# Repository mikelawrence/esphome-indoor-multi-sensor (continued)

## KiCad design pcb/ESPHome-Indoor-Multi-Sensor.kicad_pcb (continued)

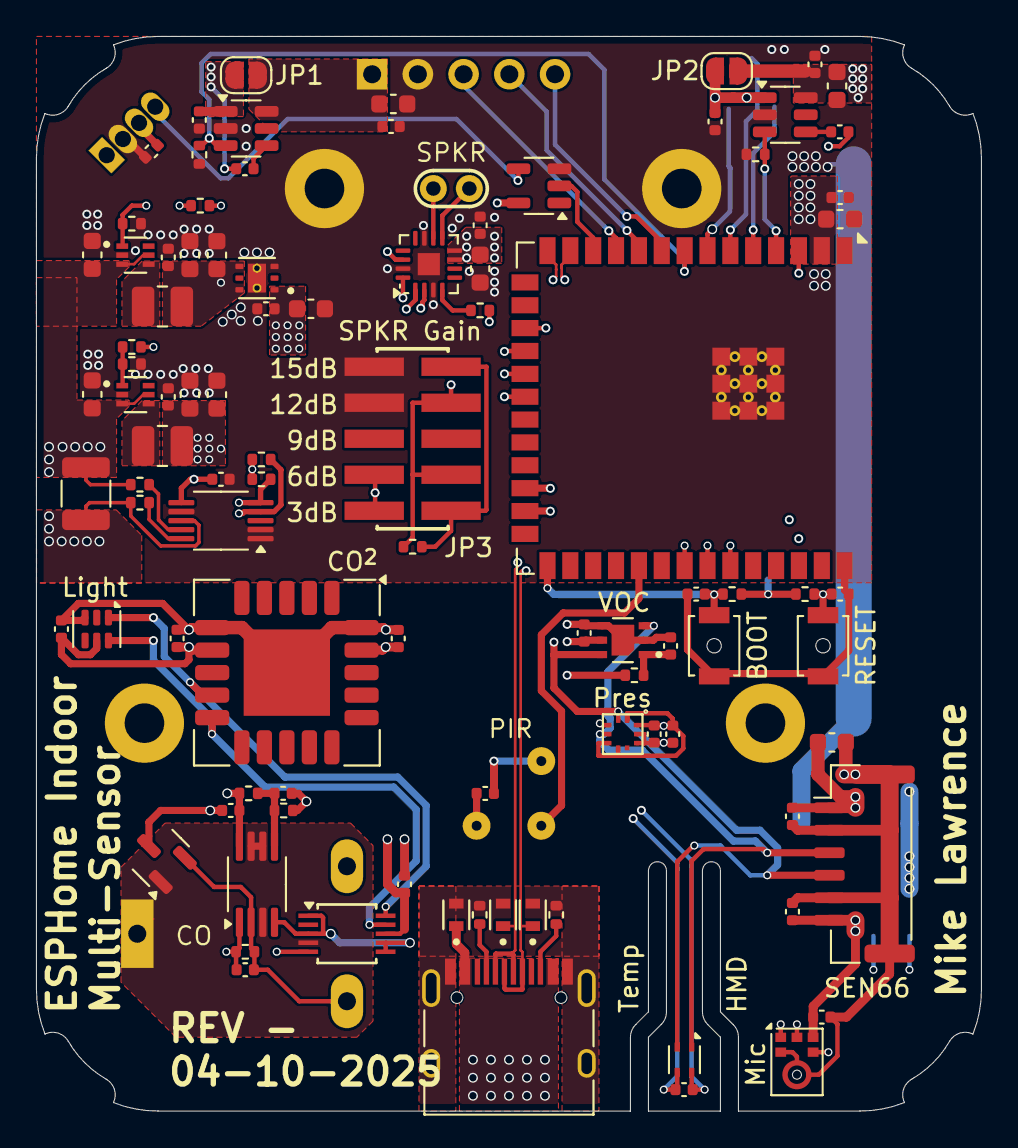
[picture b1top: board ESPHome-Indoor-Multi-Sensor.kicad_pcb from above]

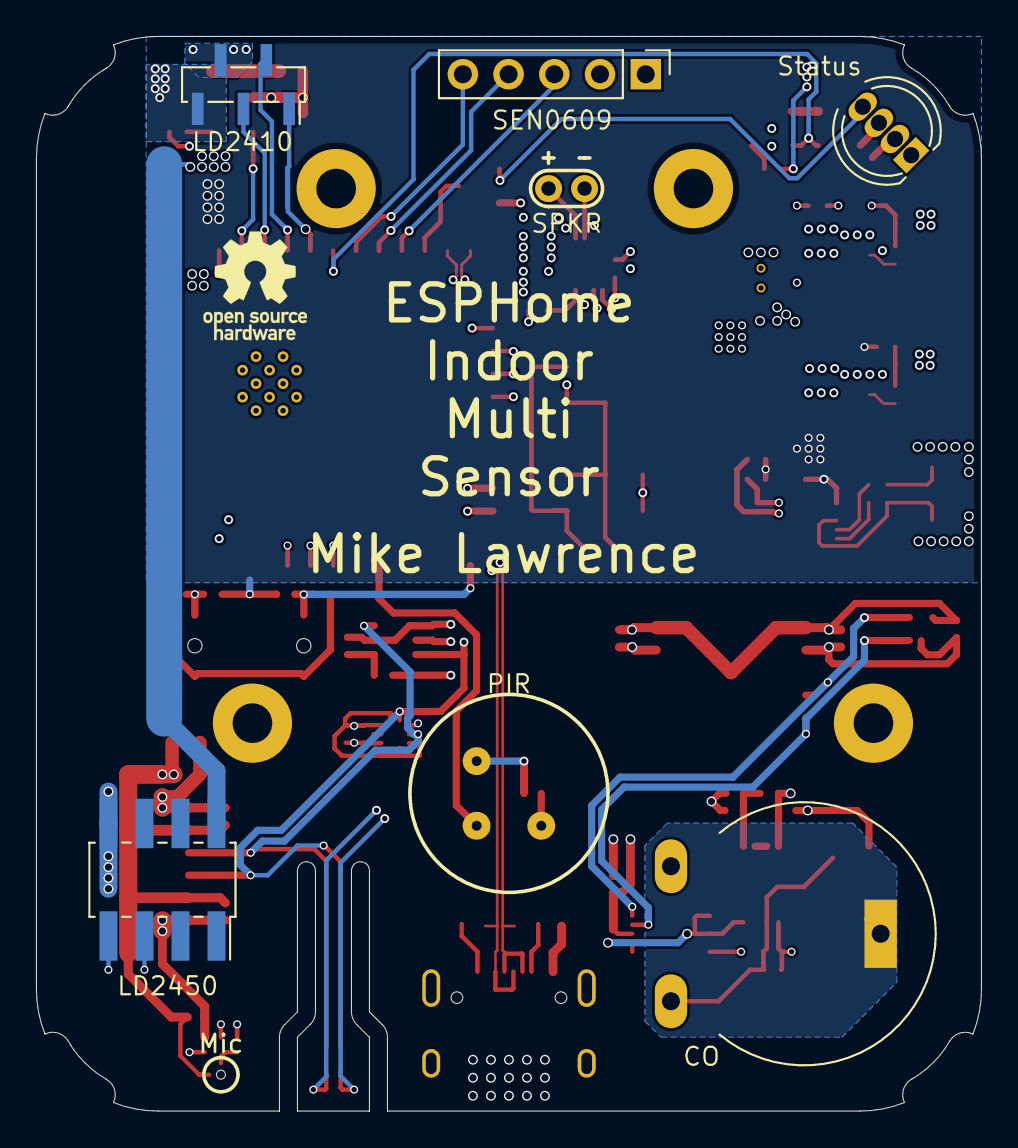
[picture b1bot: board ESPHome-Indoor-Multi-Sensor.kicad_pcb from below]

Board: 4 copper layers, 52.5 x 59.7 mm, 106 parts (8 on the bottom side), 52 nets.

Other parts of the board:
TEXT1: OSHW-Logo_5.7x6mm_SilkScreen

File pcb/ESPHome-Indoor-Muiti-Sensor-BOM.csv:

"Qty","Reference","Value","Description","DNP","Manufacturer","Part Number"
"13","C1,C4,C5,C6,C8,C26,C29,C30,C31,C35,C38,C40,C41","1uF","Capacitor, 1uF, MLCC, 25V, X5R, 10%, 0402","","Samsung","CL05A105KA5NQNC"
"16","C10,C11,C14,C18,C21,C24,C25,C27,C28,C32,C33,C36,C37,C39,C42,C43","100nF","Capacitor, 100nF, MLCC, 50V, X7R, 10%, 0402","","Samsung","CL05B104KB54PNC"
"12","C2,C3,C12,C13,C15,C16,C17,C19,C20,C22,C23,C34","22uF","Capacitor, 22uF, MLCC, 6.3V, X5R, 20%, 0603","","Murata","GRM188R60J226MEA0D"
"2","C7,C9","1nF","Capacitor, 1nF, MLCC, 50V, X7R, 10%, 0402","","KYOCERA AVX","04023C102KAT2A"
"1","D1","ESDA25P35-1U1M","TVS, Unidirectional high power, QFN-2","","STMicroelectronics","ESDA25P35-1U1M"
"1","D4","NeoPixel_THT","RGB LED with integrated controller, 5mm/8mm LED package","","Adafruit","1938"
"2","D2,D3","ESDA7P60-1U1M","TVS, Unidirectional high power, QFN-2","","STMicroelectronics","ESDA7P60-1U1M"
"1","J1","SEN66","6-Position, 1.25 mm pitch, Wire-to-Board connector","","JST","BM06B-GHS-TBT"
"1","J2","USB-C","Connector, USB 2.0, 16P, Type-C, Receptacle","","Phoenix Contact","1332645"
"1","J3","SEN0609","Generic connector, 2.54mm spacing, single row, 01x05 (TLW-105-06-T-S)","","Samtec","CES-105-01-T-S"
"1","J4","LD2410","Generic connector, 1.27mm spacing, single row, 01x05","","Samtec","RSM-105-02-S-S"
"1","J5","SPKR","Solder Holes for up to 24 ga wire","","Same Sky","CMS-251437-24SP-X8 "
"1","J6","LD2450","Socket, 8 position, 2mm spacing, dual row, 02x04, SMT","","Molex","79109-1003"
"1","JP3","Gain","Header, 10 position, 2mm spacing, dual row, 02x05, SMT","","Samtec","TMM-105-01-L-D-SM-P-TR"
"2","L1,L2","1uH","Inductor, 1uH, 3.3A, 20%, 1008","","Murata","DFE252012F-1R0M=P2"
"1","MK1","ICS-43434","TDK InvenSense MEMS Microphone, 24-bit I2S, 65 dBA SNR, LGA-6","","TDK InvenSense","ICS-43434"
"1","Q1","MMBFJ201","20mA min, 35V, 30mOhm max, 3-10V Vgs(off), N-Channel JFET, SOT-23","","Onsemi","MMBFJ201"
"1","R3","499KΩ","Resistor, 499KΩ, 62.5mW, 1%, 0402","","Vishay / Dale","CRCW0402499KFKED"
"1","R5","634KΩ","Resistor, 634KΩ, 62.5mW, 1%, 0402","","Vishay / Dale","CRCW0402634KFKED"
"1","R6","453KΩ","Resistor, 453KΩ, 62.5mW, 1%, 0402","","Vishay / Dale","CRCW0402453KFKED"
"1","R11","150mΩ","Current Sense Resistor, 150mΩ, 500mW, 1%, 1210","","Panasonic","ERJ-14BSFR15U"
"1","R16","4.7Ω","Resistor, 4.7Ω, 62.5mW, 1%, 0402","","Vishay / Dale","CRCW04024R70FKED"
"1","R17","64.9KΩ","Resistor, 64.9KΩ, 62.5mW, 1%, 0402","","Vishay / Dale","CRCW040264K9FKED "
"1","R21","133KΩ","Resistor, 133KΩ, 62.5mW, 1%, 0402","","Vishay / Dale","CRCW0402133KFKED"
"6","R1,R2,R4,R7,R13,R18","100KΩ","Resistor, 100KΩ, 62.5mW, 1%, 0402","","Vishay / Dale","CRCW0402100KFKED"
"2","R10,R12","10Ω","Resistor, 10Ω, 62.5mW, 1%, 0402","","Vishay / Dale","CRCW040210R0FKEE"
"2","R14,R15","10KΩ","Resistor, 10KΩ, 62.5mW, 1%, 0402","","Vishay / Dale","CRCW040210K0FKED"
"2","R19,R20","5.1KΩ","Resistor, 5.1KΩ, 62.5mW, 1%, 0402","","Vishay / Dale","CRCW04025K10FKED"
"2","R8,R9","DNP","Resistor, Do Not Populate, 0402","DNP","",""
"1","SW1","BOOT","Switch, SMD","","Omron","B3U-1000P"
"1","SW2","RESET","Switch, SMD","","Omron","B3U-1000P"
"1","U3","SN74LV1T34DBV","IC, Single Power Supply, Single Buffer GATE, CMOS Logic, Level Shifter, SOT-23-5","","Texas Instruments","SN74LV1T34DBV"
"1","U5","MAX98357A","Mono DAC with amplifier, I2S, PCM, TDM, 32-bit, 96khz, 3.2W, TQFP-16","","Maxim","MAX98357AETE"
"1","U6","TLV75533PDRV","500mA Low Dropout Voltage Regulator, Fixed Output 3.3V, WSON6","","Texas Instruments","TLV75533PDRV"
"1","U8","ESP32-S3-WROOM-2-N32R16V","RF Module, ESP32-S3 SoC, Wi-Fi 802.11b/g/n, Bluetooth, BLE, 32-bit, 3.3V, onboard antenna, SMD","","Espressif","ESP32-S3-WROOM-2-N32R16V"
"1","U9","INA228","IC, High-Side or Low-Side Measurement, Bi-Directional Current and Power Monitor (0-85V) with I2C, SMBus-, and PMBus-Compatible Interface, VSSOP-10","","Texas Instruments","INA228AIDGSR"
"1","U10","TSL2591","Light to digital converter, 2.7 to 3.6V Vdd, DFN-6","","AMS","TSL2591"
"1","U11","SGP41","Indoor Air Quality Sensor, MOx based, DFN-6","","Sensirion","SGP41-D-R4 "
"1","U12","SCD41","Photoacoustic CO2 sensor, I2C, 2.4-5.5 V, High accuracy  400 - 5000 ppm","","Sensirion","SCD41-D-R2"
"1","U13","BMP581","Barometric Pressure Sensor, 24-bit, Low-power and Low-noise, SMD","","Bosch Sensortec ","BMP581"
"1","U14","MCP6042","Dual Operational Amplifiers, Rail-to-Rail Input/Output, MSOP-8","","Microchip","MCP6042T-I/MS"
"1","U15","ADS1115IDGS","Ultra-Small, Low-Power, I2C-Compatible, 860-SPS, 16-Bit ADCs With Internal Reference, Oscillator, and Programmable Comparator, VSSOP-10","","Texas Instruments","ADS1115IDGS"
"1","U16","SHT45","Digital Humidity and Temperature Sensor, ±1%RH, ±0.1°C, I2C, 1.08-3.6V, 16bit, DFN-4","","Sensirion","SHT45-AD1B-R2"
"1","U17","EKMC1603111","Passive Infrared (PIR) Motion Sensor, THT","","Panasonic","EKMC1603111"
"1","U18","TGS5141","Carbon Monoxide Sensor, Long life, THT","","Figaro","TGS5141-P00"
"2","U1,U2","TPS22917DBV","1V to 5.5V, 2A, 80mΩ Ultra-Low Leakage Load Switch, SOT23-6","","Texas Instruments","TPS22917DBV"
"2","U4,U7","TLV62568DRL","High Efficiency Synchronous Buck Converter, Adjustable Output 0.6V-5.5V, 1A, SOT-563-6","","Texas Instruments","TLV62568DRL"

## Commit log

2025-04-11 Initial commit.
2025-04-12 Round out the enclosure section.
2025-04-12 Cleanup the PCB section.
2025-04-12 Add more info to the main README.
2025-04-12 SLight change to schematic.
2025-06-11 Minor changes
    Separate SEN66 on a separate I2C bus.
    Add WIFi Antenna cutout.
    Beef-up Power and Ground connections to SEN66.
2025-06-24 Add ESPHome Installation and Configuration
    Add customizable configurations
    Add Workflows to automatically build ESPHome binaries.
    Add documentation.
2025-06-24 All substitutions must be strings
2025-06-24 Remove Update Rate configuration settings
2025-06-24 Support vent_use_humidity and vent_use_co2 substitutions
2025-06-24 Add configuration details to the Github page
2025-06-24 CI Workflow changes
    CI spawns on push to dev
    CI only builds latest stable ESPHome
2025-06-24 CI only builds ESPHome stable
2025-06-24 Fix CI path error
2025-06-25 Update ci.yml
    Fix CI path error
2025-06-25 rename config files
2025-06-25 Update config file names inside config files
2025-06-25 Update ci.yml
    Allow for 4 parallel runs
2025-06-25 Correct file names in workflows
2025-06-30 Force line endings to LF
2025-06-30 Workflow updates
    Add automatic Release when merging a pull request into main.
    Next the ESP32 build process is kicked off for all config files.
    Next the build files are published to the Release as assets.
    And finally Github Pages are published supporting the new Release.
2025-06-30 Substantial config changes
    Config filenames now include esp32-s3.
    Simplification of substitutions
2025-06-30 Update Github Pages
    Finish out the config substitutions.
2025-06-30 Minor update to Github Pages
2025-06-30 Fix miss-match with Create Release workflow and downstream workflows
2025-06-30 Update Github Pages
2025-06-30 Another update to Github Pages
2025-06-30 Update publish-firmware.yml
    Eliminate checks on publish-firmware
2025-06-30 Support External Component 2591
    Fix compile ESP32 compile error
2025-06-30 Changes to TSL2591 configuration
    Looking for better low light and stopping the both sensors are 0 warning
2025-06-30 Slight Changes to Github Pages
2025-06-30 Bump cardinalby/git-get-release-action from 1.2.4 to 1.2.5
    Bumps [cardinalby/git-get-release-action](https://github.com/cardinalby/git-get-release-action) from 1.2.4 to 1.2.5.
    - [Release notes](https://github.com/cardinalby/git-get-release-action/releases)
    - [Commits](https://github.com/cardinalby/git-get-release-action/compare/1.2.4...1.2.5)
    ---
    updated-dependencies:
    - dependency-name: cardinalby/git-get-release-action
2025-06-30 CO2 changes
    Fix missing update on CO2 Calibration Date Sensor
    Configuration variable changed to automatic_self_calibration which is already in consts.py
2025-07-01 Releases are no longer automatic when PR is merger into main
2025-07-01 Include more yaml files for CI workflow
2025-07-01 Try to fix checkout in CI. PR's check out main
2025-07-01 Undo checkout changes in CI workflow
2025-07-01 Default substitution changes
2025-07-01 Remove condition that prevent this workflow from running
2025-07-02 Make sure key sensors have id's
2025-07-02 Remove condition on create-release workflow
2025-07-02 Change when to publish co2_calibration_date
2025-07-02 Update external component source
2025-07-02 Support updating when API connects for info template text sensors
2025-07-04 Lots of changes
    BMP581 128x oversample rate
    Add CO sensor long average
    Add add-speaker.yaml
    Add common_yaml
2025-07-04 Quick changes
2025-07-04 New CO warning alert
2025-07-04 Update file location
2025-07-04 speaker is now part of common.yaml
2025-07-04 Main config files now support common.yaml
2025-07-05 Back to common.yaml file approach (#12)
    * Make sure key sensors have id's
    * Remove condition on create-release workflow
    * Change when to publish co2_calibration_date
    * Update external component source
    * Support updating when API connects for info template text sensors
    * New CO warning alert
2025-07-05 PCB Rev A
2025-07-05 PCB Rev A
    Minor changes to PCB now at Rev A
2025-07-05 Add common.yaml package. Won't compile without it.
2025-07-05 yamllint cleanup
2025-07-05 Fix schematic pdf
2025-07-05 Fix messed up binary files
2025-07-05 Remove BMP581 for external components
    Switching back to ESPHome component
2025-07-05 Minor changes
    Rename Create Release workflow Create Pre-release
    Add common.yaml to installation webpage
2025-07-05 Publish Firmware workflow is now latest prerelease
2025-07-05 Publish Firmware workflow also needs the trigger name to be Pre-release
2025-07-05 Fix typo in publish firmware workflow
2025-07-06 update binary files that may have been corrupted
2025-07-07 Get back to stable
2025-07-07 Fix missing script
2025-07-07 Add new C4001 text_sensor and buttons
2025-07-07 Fix spelling error
2025-07-07 Fix duplicate text_sensor
2025-07-07 Remove extra line at the top
2025-07-07 Fix incorrect button id
2025-07-08 add dfrobot_c4001_id to drfrobot_c4001 sensors
2025-07-09 Remove configuration section
